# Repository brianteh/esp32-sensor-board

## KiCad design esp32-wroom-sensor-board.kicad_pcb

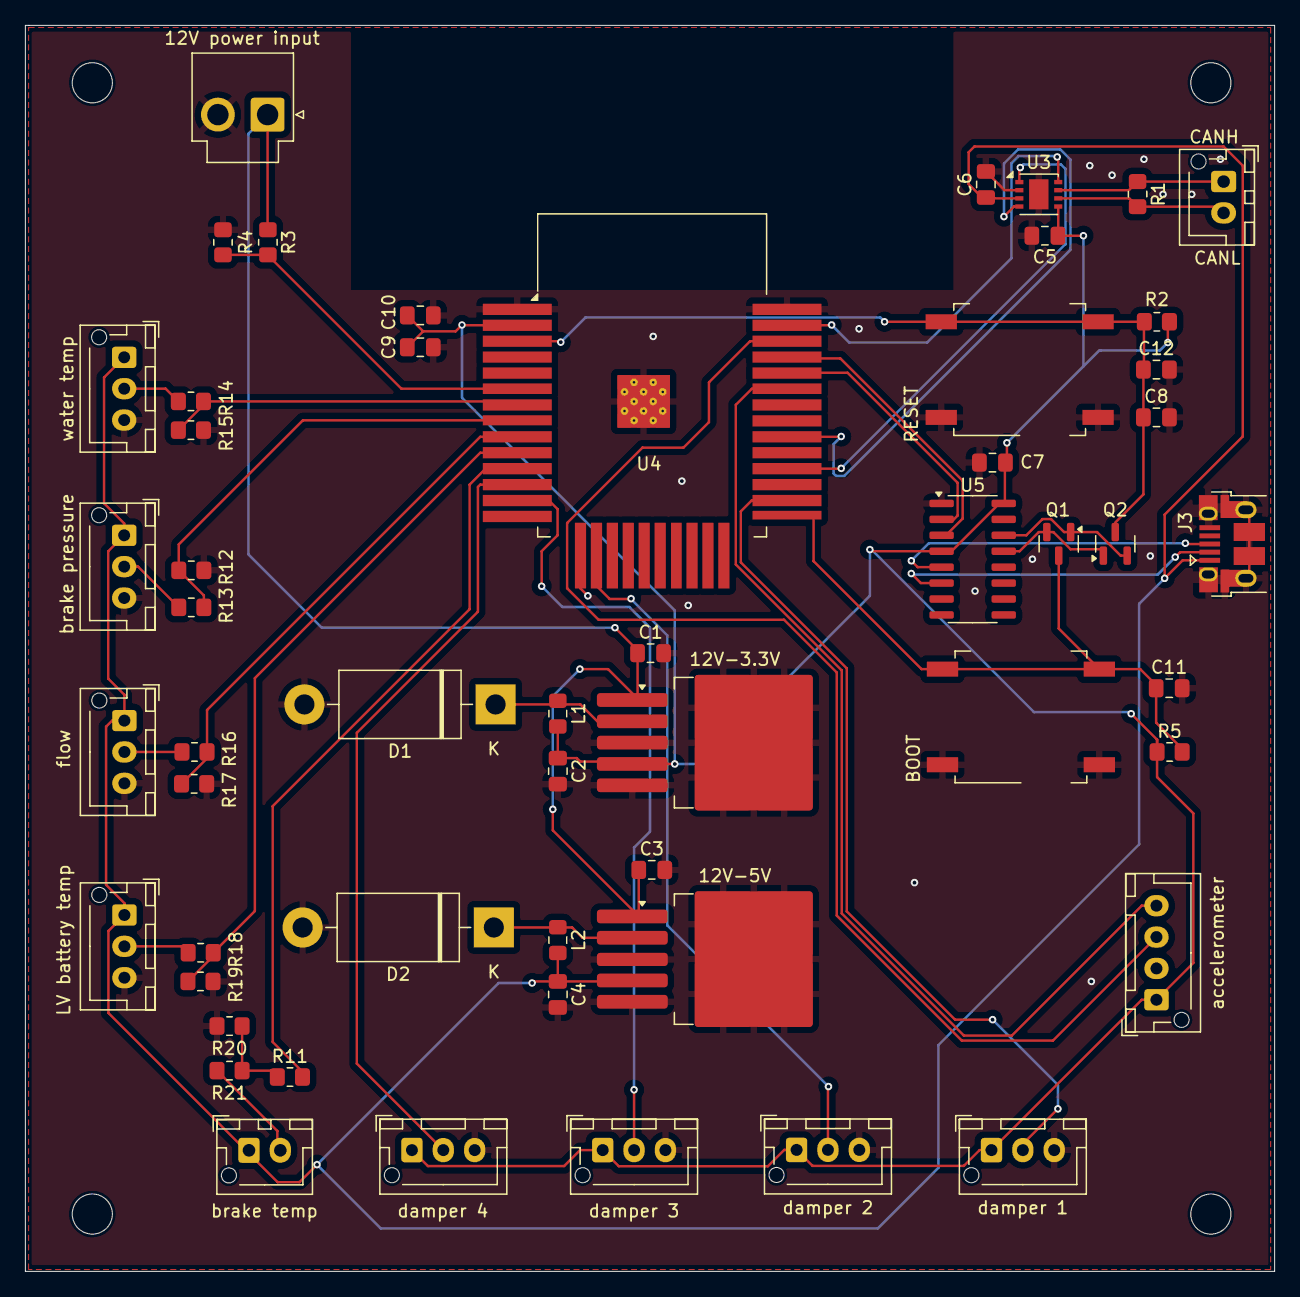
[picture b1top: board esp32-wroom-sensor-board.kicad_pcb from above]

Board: 2 copper layers, 99.6 x 99.3 mm, 58 parts (0 on the bottom side), 37 nets.

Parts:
12V power input: JST_VH_POWER; JST_VH_B2P-VH_1x02_P3.96mm_Vertical
12V-3.3V: LM2576HVS-3.3; TO-263-5_TabPin3
12V-5V: LM2576HVS-5; TO-263-5_TabPin3
BOOT: BOOT1; SW_MEC_5GSH9
C1, C3: 100uF; C_0805_2012Metric_Pad1.18x1.45mm_HandSolder
C2, C4: 1000uF; C_0805_2012Metric_Pad1.18x1.45mm_HandSolder
C5, C6, C7, C9, C11, C12: 100nF; C_0805_2012Metric_Pad1.18x1.45mm_HandSolder
C8: 1uF; C_0805_2012Metric_Pad1.18x1.45mm_HandSolder
C10: 10uF; C_0805_2012Metric_Pad1.18x1.45mm_HandSolder
CANH: JST_XH_CAN; JST_XH_B2B-XH-AM_1x02_P2.50mm_Vertical
D1, D2: 1N5822; D_DO-201AD_P15.24mm_Horizontal
H1, H2, H3, H4: MountingHole; MountingHole_3.2mm_M3
J3: USB_B_Micro; USB_Micro-B_Amphenol_10103594-0001LF_Horizontal
L1, L2: 100uH; L_0805_2012Metric_Pad1.15x1.40mm_HandSolder
LV battery temp: JST_XH_LVBT; JST_XH_B3B-XH-AM_1x03_P2.50mm_Vertical
Q1, Q2: BSS138; SOT-23
R1: 120R; R_0805_2012Metric_Pad1.20x1.40mm_HandSolder
R2, R5: 10k; R_0805_2012Metric_Pad1.20x1.40mm_HandSolder
R3, R13, R14, R16, R18, R20: 43R; R_0805_2012Metric_Pad1.20x1.40mm_HandSolder
R4, R12, R15, R17, R19, R21: 82R; R_0805_2012Metric_Pad1.20x1.40mm_HandSolder
R11: ?; R_0805_2012Metric_Pad1.20x1.40mm_HandSolder
RESET: RESET1; SW_MEC_5GSH9
U3: TJA1051TK-3; DFN-8-1EP_3x3mm_P0.65mm_EP1.55x2.4mm
U4: ESP32-WROOM-32
U5: CH340C; SOIC-16_3.9x9.9mm_P1.27mm
accelerometer: JST_XH_MPU; JST_XH_B4B-XH-AM_1x04_P2.50mm_Vertical
brake pressure: JST_XH_BP; JST_XH_B3B-XH-AM_1x03_P2.50mm_Vertical
brake temp: JST_XH_BTS; JST_XH_B2B-XH-AM_1x02_P2.50mm_Vertical
damper 1: JST_XH_DT1; JST_XH_B3B-XH-AM_1x03_P2.50mm_Vertical
damper 2: JST_XH_DT2; JST_XH_B3B-XH-AM_1x03_P2.50mm_Vertical
damper 3: JST_XH_DT3; JST_XH_B3B-XH-AM_1x03_P2.50mm_Vertical
damper 4: JST_XH_DT4; JST_XH_B3B-XH-AM_1x03_P2.50mm_Vertical
flow: JST_XH_FS; JST_XH_B3B-XH-AM_1x03_P2.50mm_Vertical
water temp: JST_XH_WT; JST_XH_B3B-XH-AM_1x03_P2.50mm_Vertical

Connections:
+3.3V: 12V-3.3V.4 (FB), C2.1, C5.1, C7.1, C9.1, C10.1, L1.2, R2.1, R5.1, U3.5 (VIO), U4.2 (VDD), U5.4 (V3), U5.16 (VCC), accelerometer.1, damper 1.1, damper 2.1, damper 3.1, damper 4.1
+5V: 12V-5V.4 (FB), C4.1, C6.1, J3.1 (VBUS), L2.2, LV battery temp.1, U3.3 (VCC), brake pressure.1, brake temp.1, flow.1, water temp.1
/ADC_BP: R12.1, R13.2, U4.8 (IO32)
/ADC_BTS: R11.2, U4.11 (IO26)
/ADC_DT1: U4.26 (IO4), damper 1.2
/ADC_DT2: U4.16 (IO13), damper 2.2
/ADC_DT3: U4.13 (IO14), damper 3.2
/ADC_DT4: U4.12 (IO27), damper 4.2
/ADC_FS: R16.2, R17.1, U4.9 (IO33)
/ADC_LVBT: R18.2, R19.1, U4.10 (IO25)
/ADC_LVBV: R3.2, R4.1, U4.6 (IO34)
/ADC_WT: R14.2, R15.1, U4.7 (IO35)
/CANH: CANH.1, R1.1, U3.7 (CANH)
/CANL: CANH.2, R1.2, U3.6 (CANL)
/CAN_RX: U3.4 (RXD), U4.30 (IO18)
/CAN_S: U3.8 (S), U4.37 (IO23)
/CAN_TX: U3.1 (TXD), U4.28 (IO17)
/EN: C8.1, C12.1, Q1.3 (D), R2.2, RESET.3 (K), RESET.4 (A), U4.3 (EN)
/IO0: BOOT.3 (K), BOOT.4 (A), C11.1, Q2.3 (D), R5.2, U4.25 (IO0)
/POWER_INPUT: 12V power input.1, 12V-3.3V.1 (VIN), 12V-5V.1 (VIN), C1.1, C3.1, R3.1
/SCL: U4.36 (IO22), accelerometer.3
/SDA: U4.33 (IO21), accelerometer.4
/UART_RX: U4.34 (RXD0/IO3), U5.2 (TXD)
/UART_TX: U4.35 (TXD0/IO1), U5.3 (RXD)
GND: 12V power input.2, 12V-3.3V.3 (GND), 12V-3.3V.5 (~ON/OFF), 12V-5V.3 (GND), 12V-5V.5 (~ON/OFF), BOOT.1, BOOT.2, C1.2, C2.2, C3.2, C4.2, C5.2, C6.2, C7.2, C8.2, C9.2, C10.2, C11.2, C12.2, D1.2 (A), D2.2 (A), J3.5 (GND), J3.6 (Shield), LV battery temp.3, R4.2, R12.2, R15.2, R17.2, R19.2, R21.2, RESET.1, RESET.2, U3.2 (GND), U3.9 (GND), U4.1 (GND), U4.15 (GND), U4.38 (GND), U4.39 (GND), U5.1 (GND), accelerometer.2, brake pressure.3, damper 1.3, damper 2.3, damper 3.3, damper 4.3, flow.3, water temp.3
unnamed: 12V-3.3V.2 (OUT), D1.1 (K), L1.1
unnamed: 12V-5V.2 (OUT), D2.1 (K), L2.1
unnamed: J3.3 (D+), U5.5 (UD+)
unnamed: J3.2 (D-), U5.6 (UD-)
unnamed: R13.1, brake pressure.2
unnamed: R14.1, water temp.2
unnamed: R16.1, flow.2
unnamed: LV battery temp.2, R18.1
unnamed: R20.1, brake temp.2
unnamed: Q1.1 (G), Q2.2 (S), U5.13 (~DTR)
unnamed: Q1.2 (S), Q2.1 (G), U5.14 (~RTS)
unnamed: R11.1, R20.2, R21.1

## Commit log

2025-03-01 esp32 sensor board final version
2025-03-01 minor fix
